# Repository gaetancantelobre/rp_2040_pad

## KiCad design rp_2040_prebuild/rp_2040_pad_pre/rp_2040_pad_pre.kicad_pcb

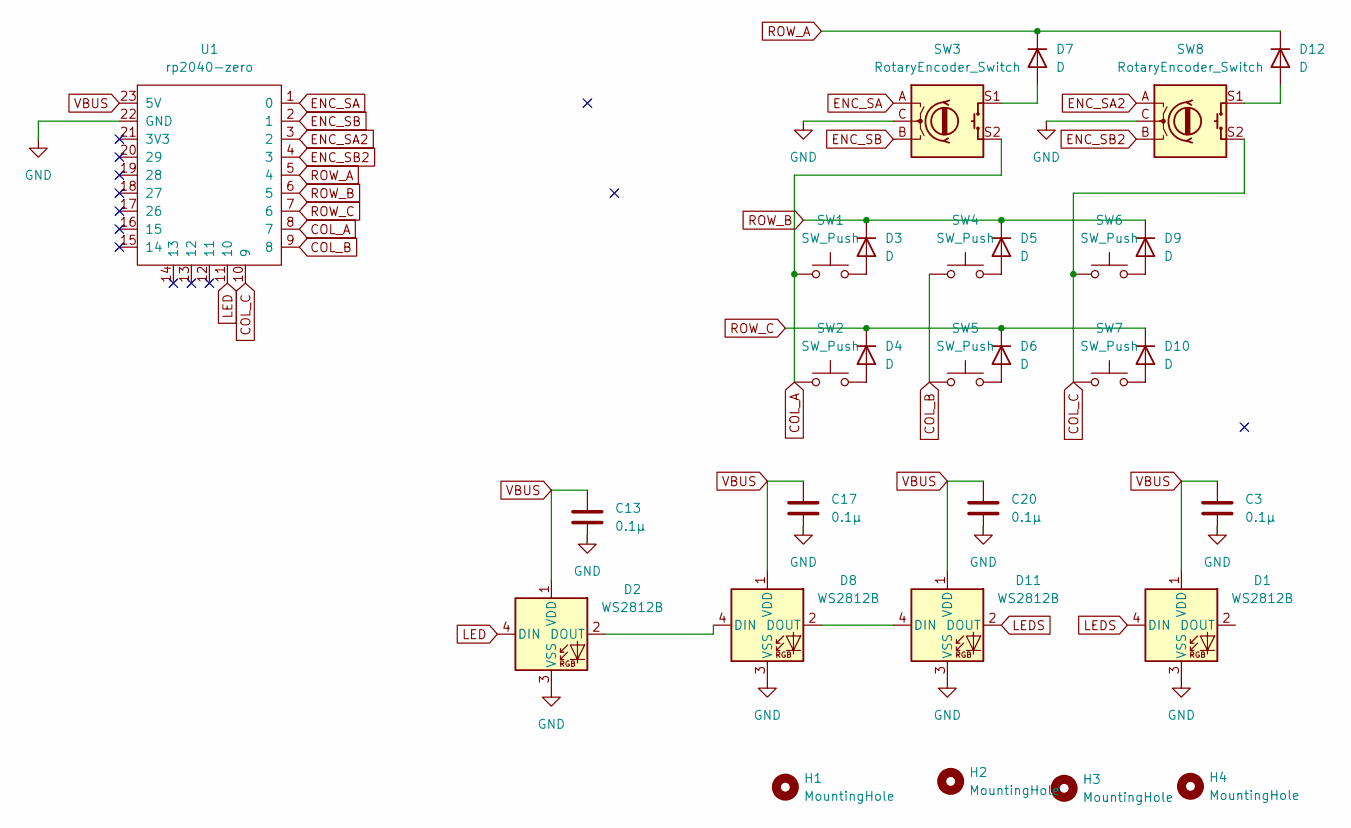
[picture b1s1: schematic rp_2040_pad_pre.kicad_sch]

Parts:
C3, C13, C17, C20: 0.1µ; C_1206_3216Metric
D1, D2, D8, D11: WS2812B; LED_WS2812B_PLCC4_5.0x5.0mm_P3.2mm
D3, D4, D5, D6, D7, D9, D10, D12: D; D_SOD-323_HandSoldering
H1, H2, H3, H4: MountingHole; MountingHole_2.2mm_M2
SW1, SW2, SW4, SW5, SW6, SW7: SW_Push; SW_Cherry_MX_1.00u_PCB
SW3, SW8: RotaryEncoder_Switch; RotaryEncoder_Alps_EC11E-Switch_Vertical_H20mm_CircularMoun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
U1: rp2040-zero; rp2040-zero-tht

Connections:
COL_A: SW1.1, SW2.1, SW3.S2, U1.8 (7)
COL_B: SW4.1, SW5.1, U1.9 (8)
COL_C: SW6.1, SW7.1, SW8.S2, U1.10 (9)
ENC_SA: SW3.A, U1.1 (0)
ENC_SA2: SW8.A, U1.3 (2)
ENC_SB: SW3.B, U1.2 (1)
ENC_SB2: SW8.B, U1.4 (3)
GND: C3.2, C13.2, C17.2, C20.2, D1.3 (VSS), D2.3 (VSS), D8.3 (VSS), D11.3 (VSS), SW3.C, SW8.C, U1.22 (GND)
LED: D2.4 (DIN), U1.11 (10)
LEDS: D1.4 (DIN), D11.2 (DOUT)
unnamed: D2.2 (DOUT), D8.4 (DIN)
unnamed: D3.2 (A), SW1.2
unnamed: D4.2 (A), SW2.2
unnamed: D5.2 (A), SW4.2
unnamed: D6.2 (A), SW5.2
unnamed: D7.2 (A), SW3.S1
unnamed: D9.2 (A), SW6.2
unnamed: D10.2 (A), SW7.2
unnamed: D8.2 (DOUT), D11.4 (DIN)
unnamed: D12.2 (A), SW8.S1
ROW_A: D7.1 (K), D12.1 (K), U1.5 (4)
ROW_B: D3.1 (K), D5.1 (K), D9.1 (K), U1.6 (5)
ROW_C: D4.1 (K), D6.1 (K), D10.1 (K), U1.7 (6)
VBUS: C3.1, C13.1, C17.1, C20.1, D1.1 (VDD), D2.1 (VDD), D8.1 (VDD), D11.1 (VDD), U1.23 (5V)

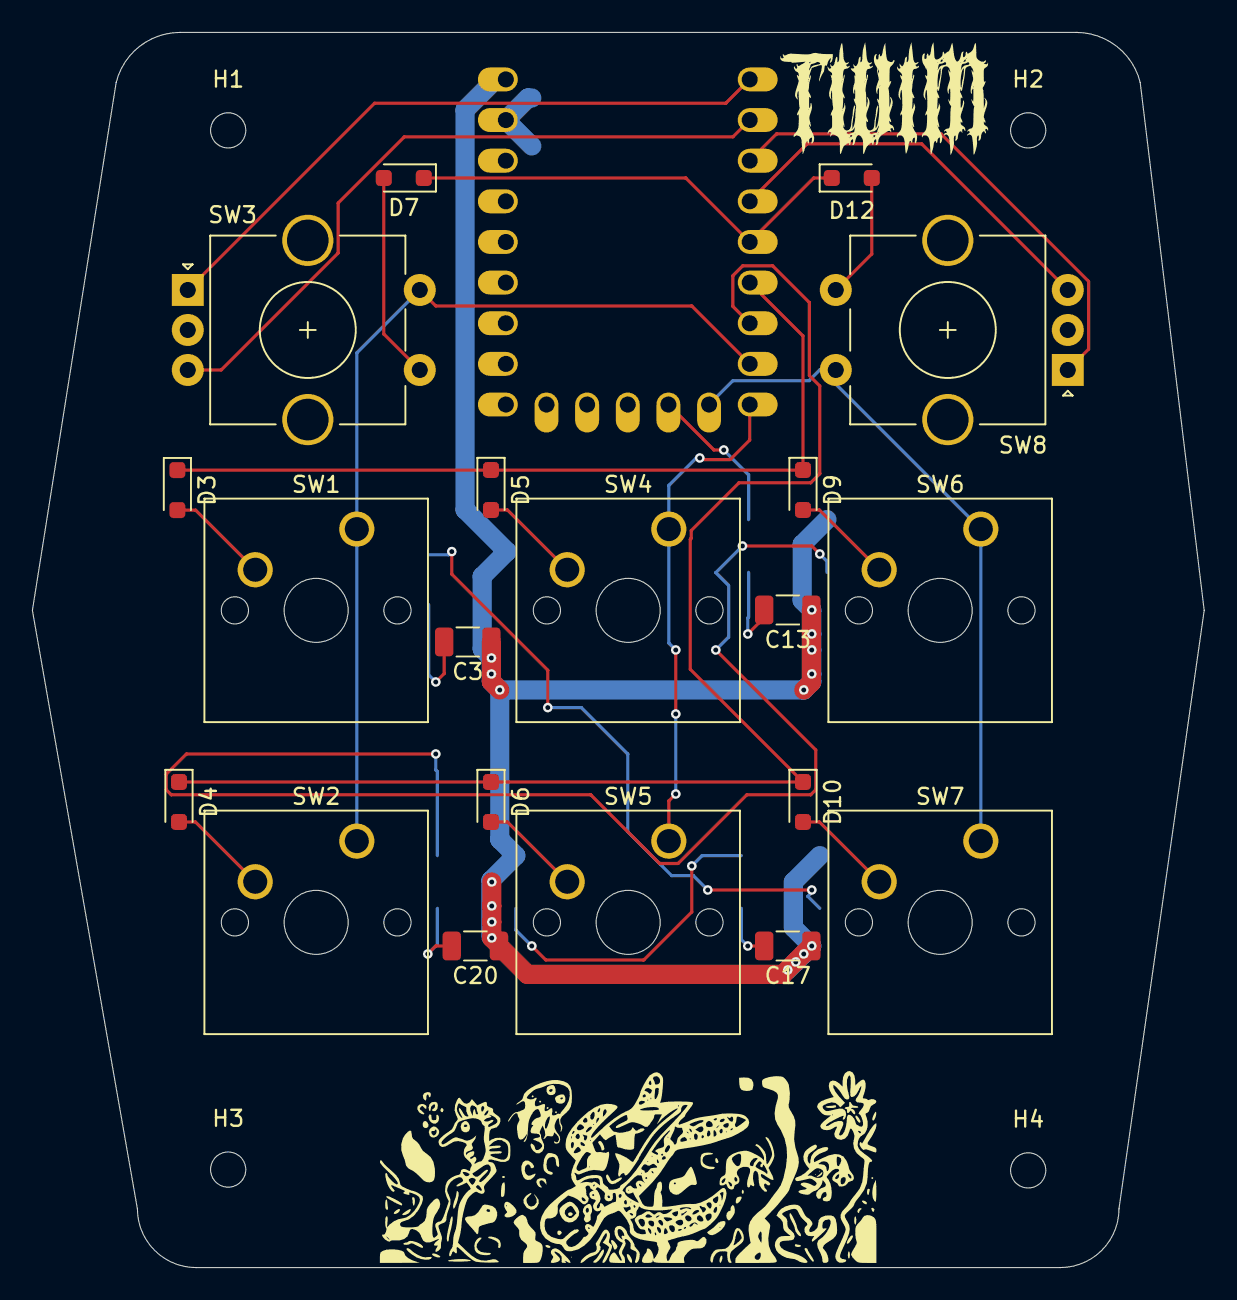
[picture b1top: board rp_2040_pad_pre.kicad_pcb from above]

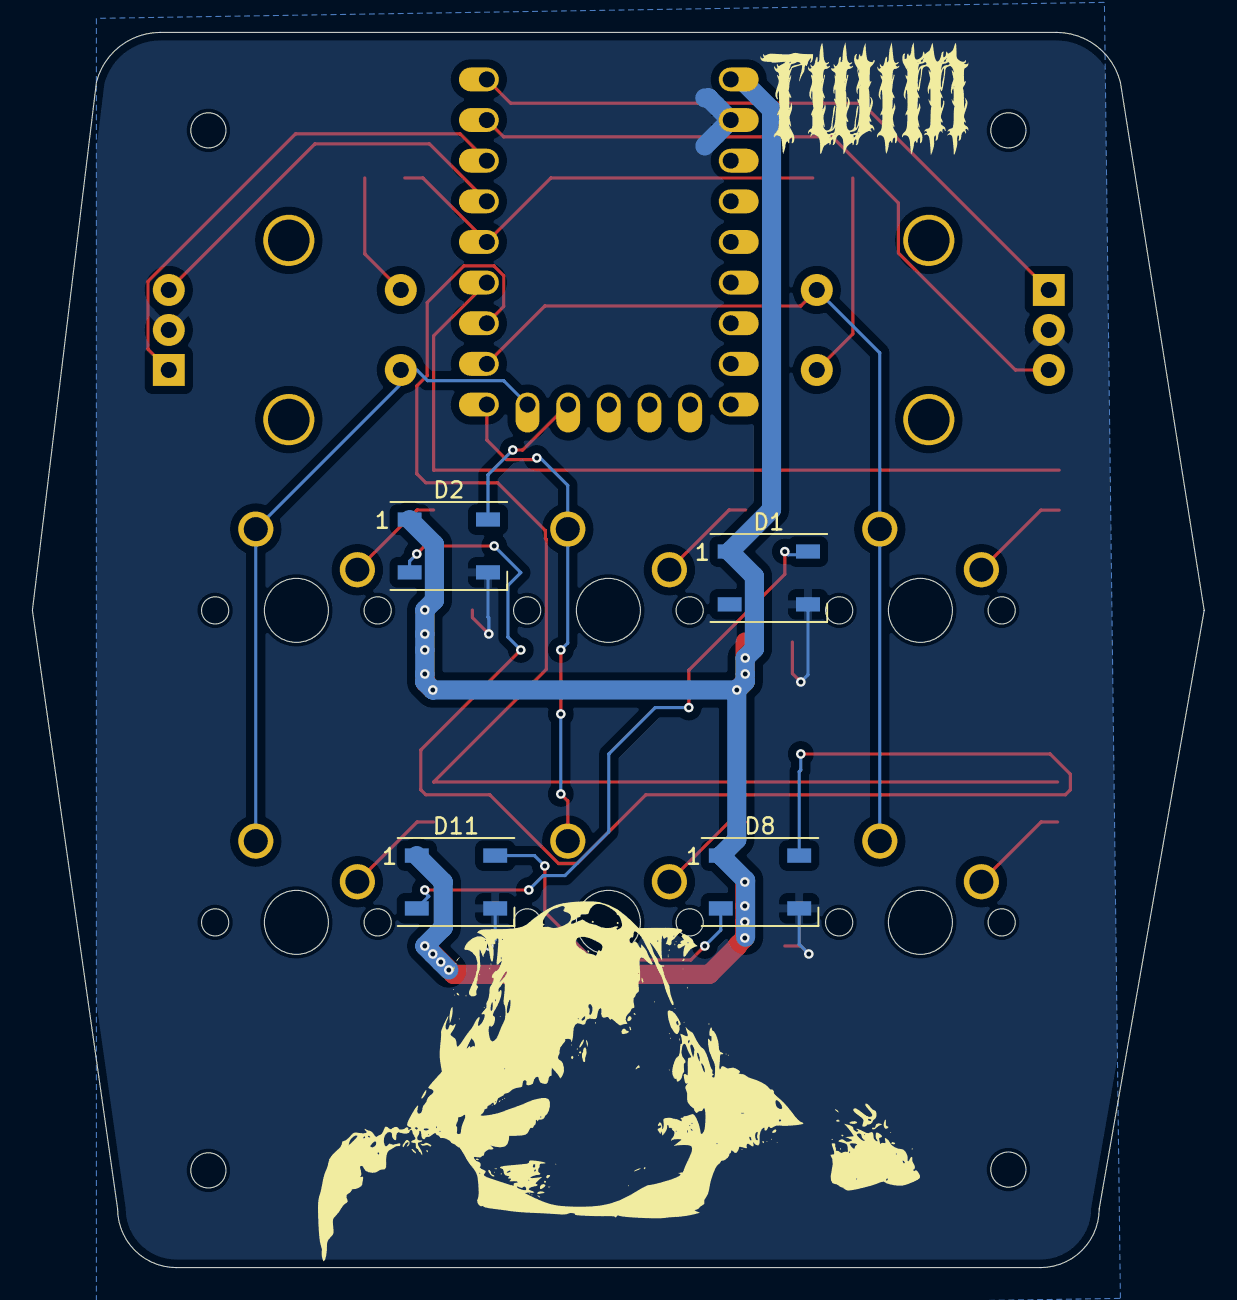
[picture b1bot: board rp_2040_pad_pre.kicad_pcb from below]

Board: 2 copper layers, 73.2 x 77.2 mm, 29 parts (4 on the bottom side), 24 nets.

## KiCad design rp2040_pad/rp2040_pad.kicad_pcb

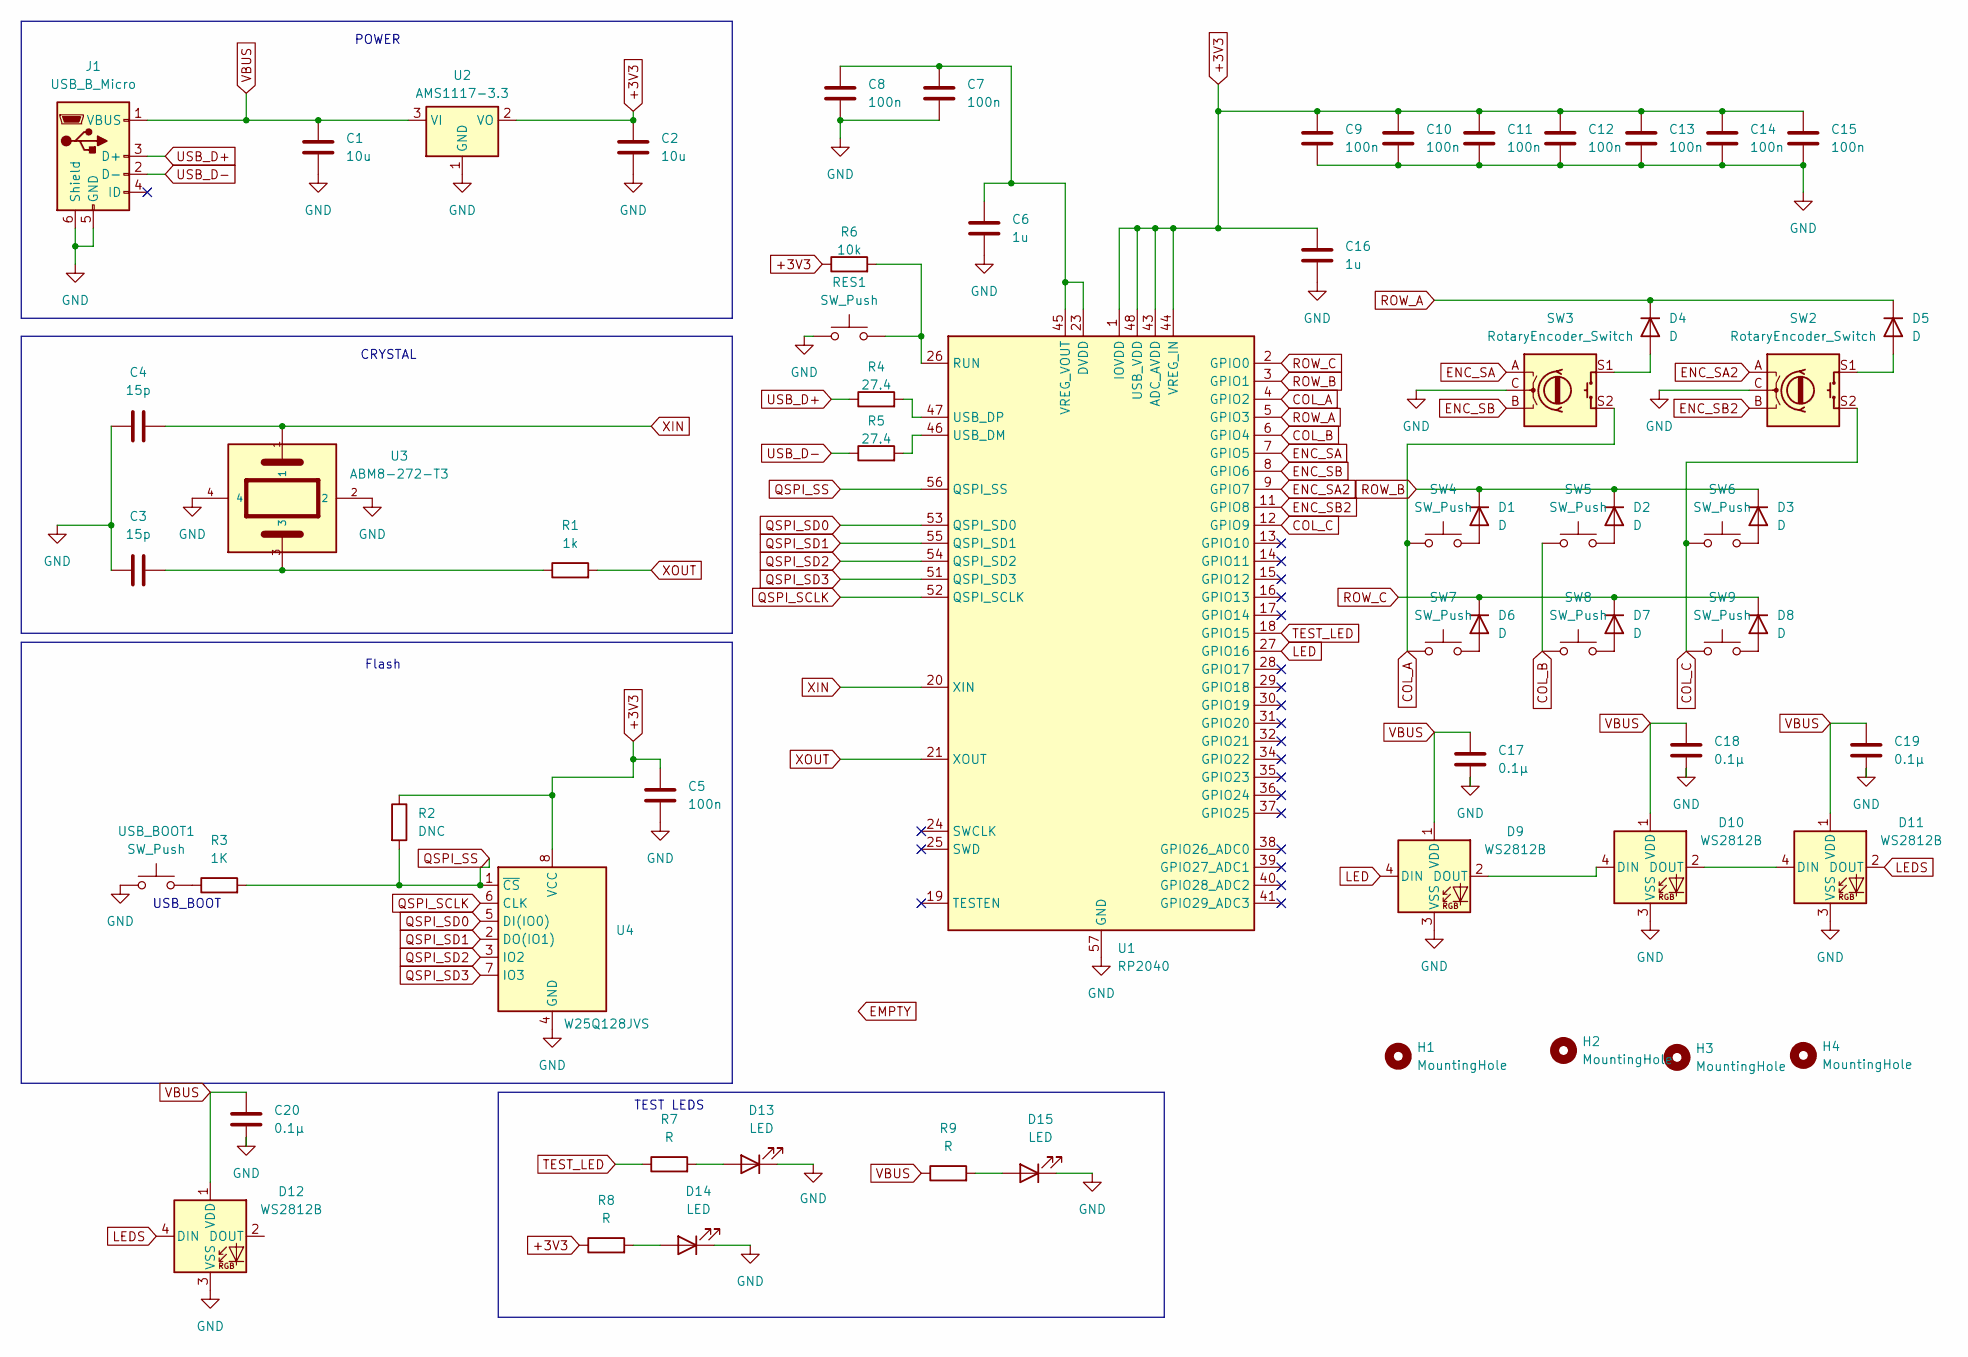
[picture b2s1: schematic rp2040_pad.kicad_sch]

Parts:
C1, C2: 10u; C_1206_3216Metric
C3, C4: 15p; C_1206_3216Metric
C5, C7, C8, C9, C10, C11, C12, C13, C14, C15: 100n; C_1206_3216Metric
C6, C16: 1u; C_1206_3216Metric
C17, C18, C19, C20: 0.1µ; C_0805_2012Metric_Pad1.18x1.45mm_HandSolder
D1, D2, D3, D4, D5, D6, D7, D8: D; D_SOD-323_HandSoldering
D9, D10, D11, D12: WS2812B; LED_WS2812B_PLCC4_5.0x5.0mm_P3.2mm
D13, D14, D15: LED; L_1206_3216Metric
H1, H2, H3, H4: MountingHole; MountingHole_3mm
J1: USB_B_Micro; USB_Micro-B_Amphenol_10103594-0001LF_Horizontal
R1: 1k; R_1206_3216Metric
R2: DNC; R_1206_3216Metric
R3: 1K; R_1206_3216Metric
R4, R5: 27.4; R_1206_3216Metric
R6: 10k; R_1206_3216Metric
R7, R8, R9: R; R_1206_3216Metric
RES1: SW_Push; SW_PUSH_6mm
SW2, SW3: RotaryEncoder_Switch; RotaryEncoder_Alps_EC11E-Switch_Vertical_H20mm_CircularMoun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
SW4, SW5, SW6, SW7, SW8, SW9: SW_Push; SW_Cherry_MX_1.00u_PCB
U1: RP2040; QFN-56-1EP_7x7mm_P0.4mm_EP3.2x3.2mm
U2: AMS1117-3.3; SOT-223-3_TabPin2
U3: ABM8-272-T3; ABM8-272-T3-crystal
U4: W25Q128JVS; SOIC-8_5.23x5.23mm_P1.27mm
USB_BOOT1: SW_Push; SW_PUSH_6mm

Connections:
+3V3: C2.1, C5.1, C9.1, C10.1, C11.1, C12.1, C13.1, C14.1, C15.1, C16.1, R2.1, R6.1, R8.1, U1.1 (IOVDD), U1.10 (IOVDD), U1.22 (IOVDD), U1.33 (IOVDD), U1.42 (IOVDD), U1.43 (ADC_AVDD), U1.44 (VREG_IN), U1.48 (USB_VDD), U1.49 (IOVDD), U2.2 (VO), U4.8 (VCC)
COL_A: SW3.S2, SW4.1, SW7.1, U1.4 (GPIO2)
COL_B: SW5.1, SW8.1, U1.6 (GPIO4)
COL_C: SW2.S2, SW6.1, SW9.1, U1.12 (GPIO9)
ENC_SA: SW3.A, U1.7 (GPIO5)
ENC_SA2: SW2.A, U1.9 (GPIO7)
ENC_SB: SW3.B, U1.8 (GPIO6)
ENC_SB2: SW2.B, U1.11 (GPIO8)
GND: C1.2, C2.2, C3.1, C4.1, C5.2, C6.2, C7.2, C8.2, C9.2, C10.2, C11.2, C12.2, C13.2, C14.2, C15.2, C16.2, C17.2, C18.2, C19.2, C20.2, D9.3 (VSS), D10.3 (VSS), D11.3 (VSS), D12.3 (VSS), D13.1 (K), D14.1 (K), D15.1 (K), J1.5 (GND), J1.6 (Shield), RES1.1, SW2.C, SW3.C, U1.57 (GND), U2.1 (GND), U3.2, U3.4, U4.4 (GND), USB_BOOT1.1; also elsewhere on the board
LED: D9.4 (DIN), U1.27 (GPIO16)
LEDS: D11.2 (DOUT), D12.4 (DIN)
unnamed: C3.2, R1.1, U3.3
unnamed: D1.2 (A), SW4.2
unnamed: D2.2 (A), SW5.2
unnamed: D3.2 (A), SW6.2
unnamed: D4.2 (A), SW3.S1
unnamed: D5.2 (A), SW2.S1
unnamed: D6.2 (A), SW7.2
unnamed: D7.2 (A), SW8.2
unnamed: D8.2 (A), SW9.2
unnamed: D9.2 (DOUT), D10.4 (DIN)
unnamed: D10.2 (DOUT), D11.4 (DIN)
unnamed: D13.2 (A), R7.2
unnamed: D14.2 (A), R8.2
unnamed: D15.2 (A), R9.2
unnamed: R3.1, USB_BOOT1.2
unnamed 26: R6.2, RES1.2, U1.26 (RUN); also elsewhere on the board
unnamed: R5.2, U1.46 (USB_DM)
unnamed: R4.2, U1.47 (USB_DP)
unnamed: C6.1, C7.1, C8.1, U1.23 (DVDD), U1.45 (VREG_VOUT), U1.50 (DVDD)
QSPI_SCLK: U1.52 (QSPI_SCLK), U4.6 (CLK)
QSPI_SD0: U1.53 (QSPI_SD0), U4.5 (DI(IO0))
QSPI_SD1: U1.55 (QSPI_SD1), U4.2 (DO(IO1))
QSPI_SD2: U1.54 (QSPI_SD2), U4.3 (IO2)
QSPI_SD3: U1.51 (QSPI_SD3), U4.7 (IO3)
QSPI_SS: R2.2, R3.2, U1.56 (QSPI_SS), U4.1 (~CS)
ROW_A: D4.1 (K), D5.1 (K), U1.5 (GPIO3)
ROW_B: D1.1 (K), D2.1 (K), D3.1 (K), U1.3 (GPIO1)
ROW_C: D6.1 (K), D7.1 (K), D8.1 (K), U1.2 (GPIO0)
TEST_LED: R7.1, U1.18 (GPIO15)
USB_D+: J1.3 (D+), R4.1
USB_D-: J1.2 (D-), R5.1
VBUS: C1.1, C17.1, C18.1, C19.1, C20.1, D9.1 (VDD), D10.1 (VDD), D11.1 (VDD), D12.1 (VDD), J1.1 (VBUS), R9.1, U2.3 (VI)
XIN: C4.2, U1.20 (XIN), U3.1
XOUT: R1.2, U1.21 (XOUT)

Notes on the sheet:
TEST LEDS
USB_BOOT
POWER
CRYSTAL
Flash

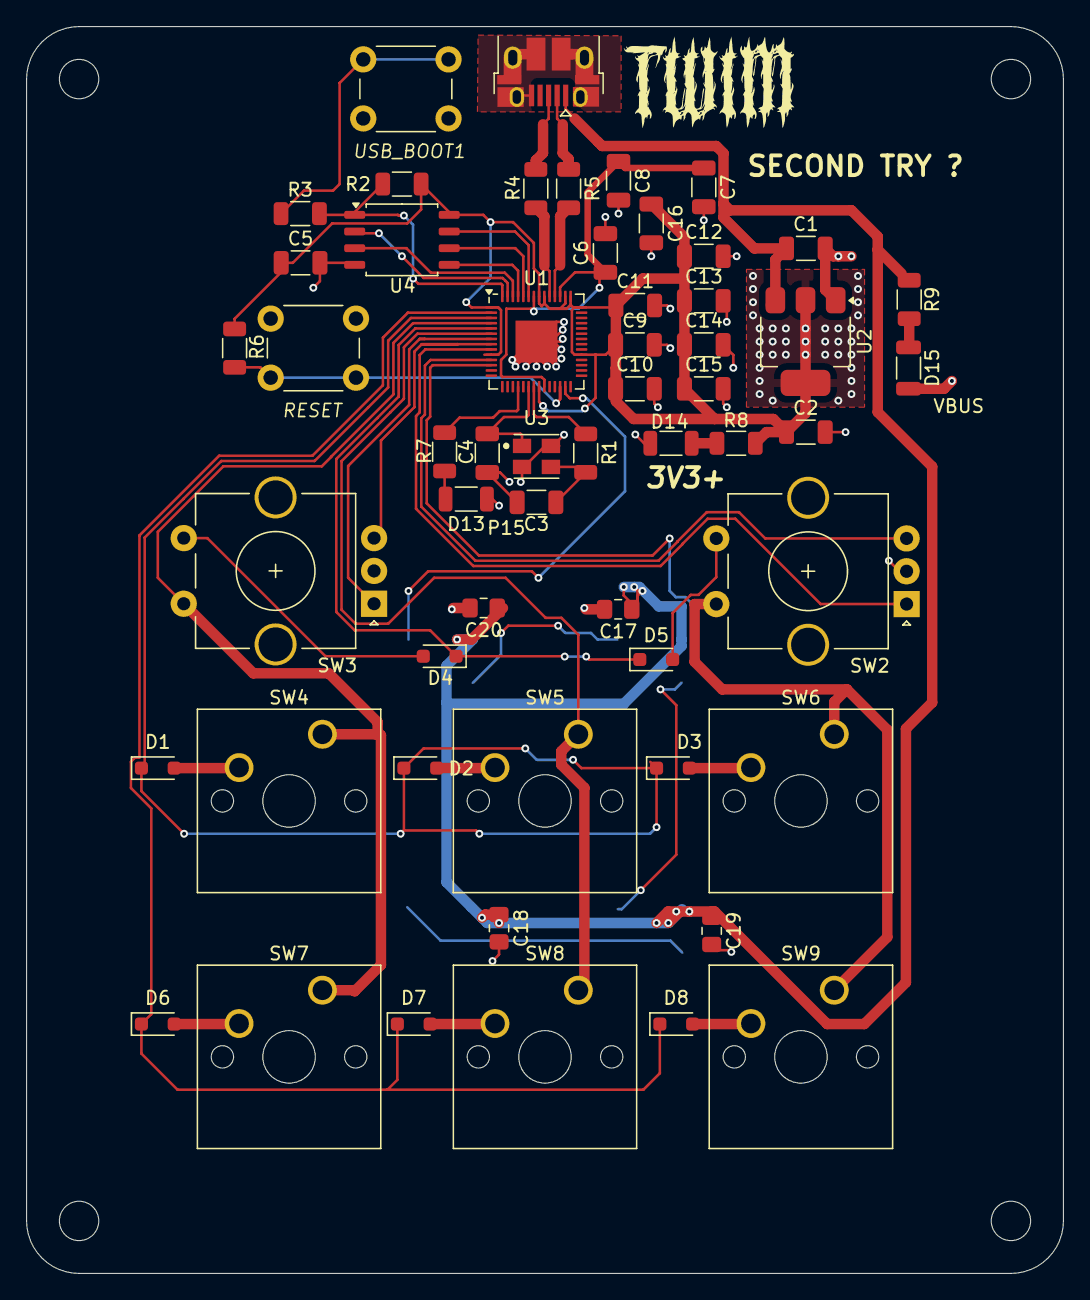
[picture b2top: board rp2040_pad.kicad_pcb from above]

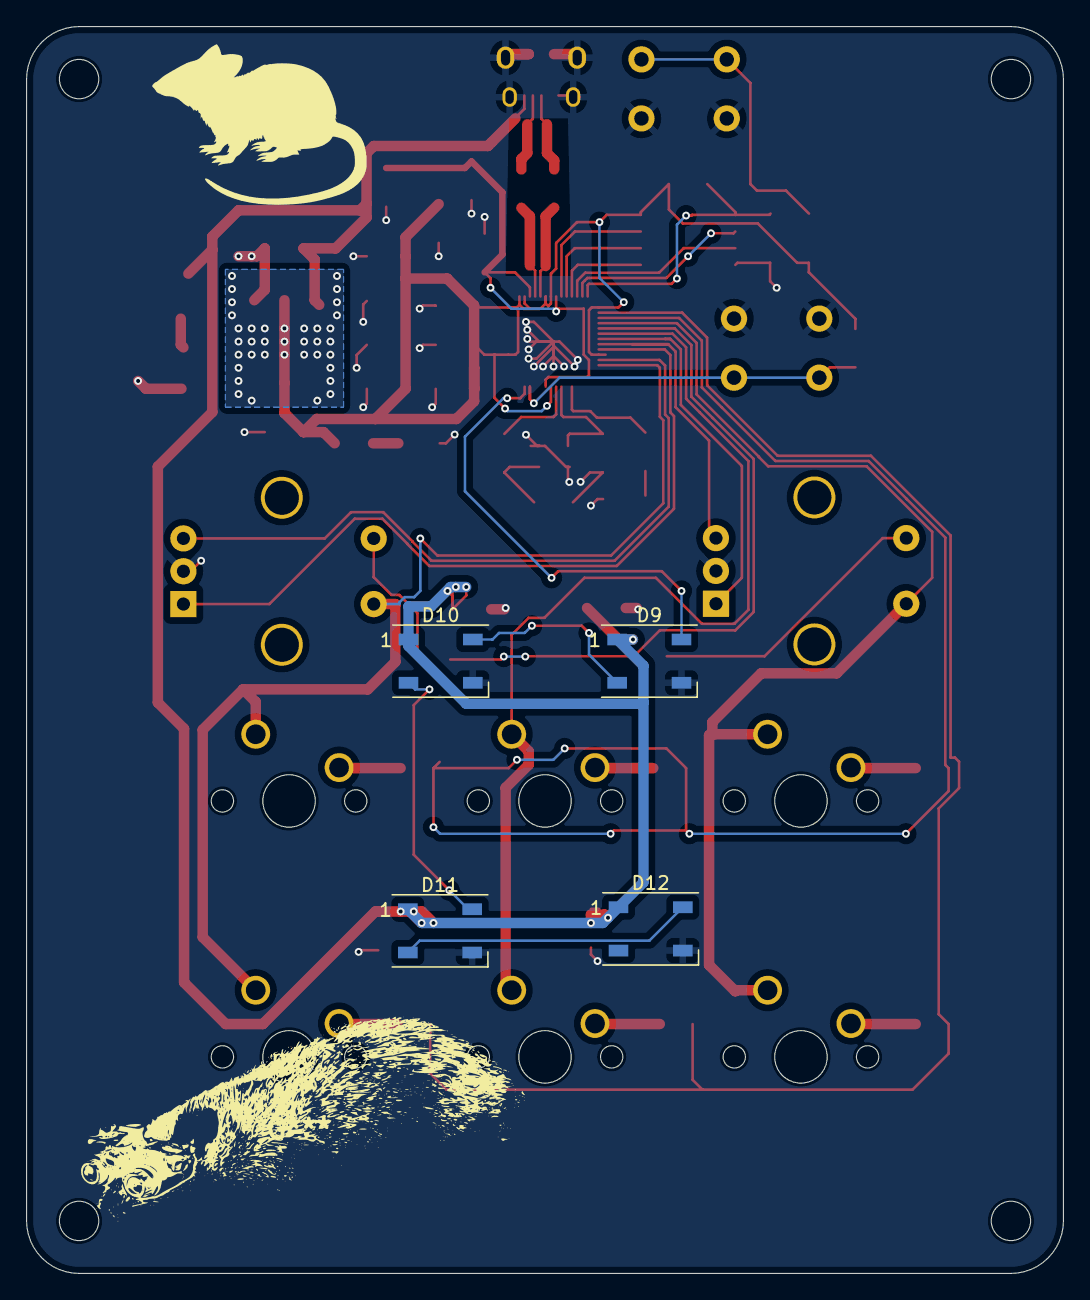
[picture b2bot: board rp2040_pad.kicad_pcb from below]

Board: 2 copper layers, 79.0 x 95.0 mm, 63 parts (4 on the bottom side), 45 nets.

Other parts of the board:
RESET: SW_Push; SW_PUSH_6mm

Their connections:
GND: RESET.1; also elsewhere on the board
unnamed 26: RESET.2; also elsewhere on the board

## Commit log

2025-01-23 added all the files
2025-01-27 new design
2025-01-30 added final version
2025-03-26 added a bunch of stuff
2025-11-15 added qmk code
